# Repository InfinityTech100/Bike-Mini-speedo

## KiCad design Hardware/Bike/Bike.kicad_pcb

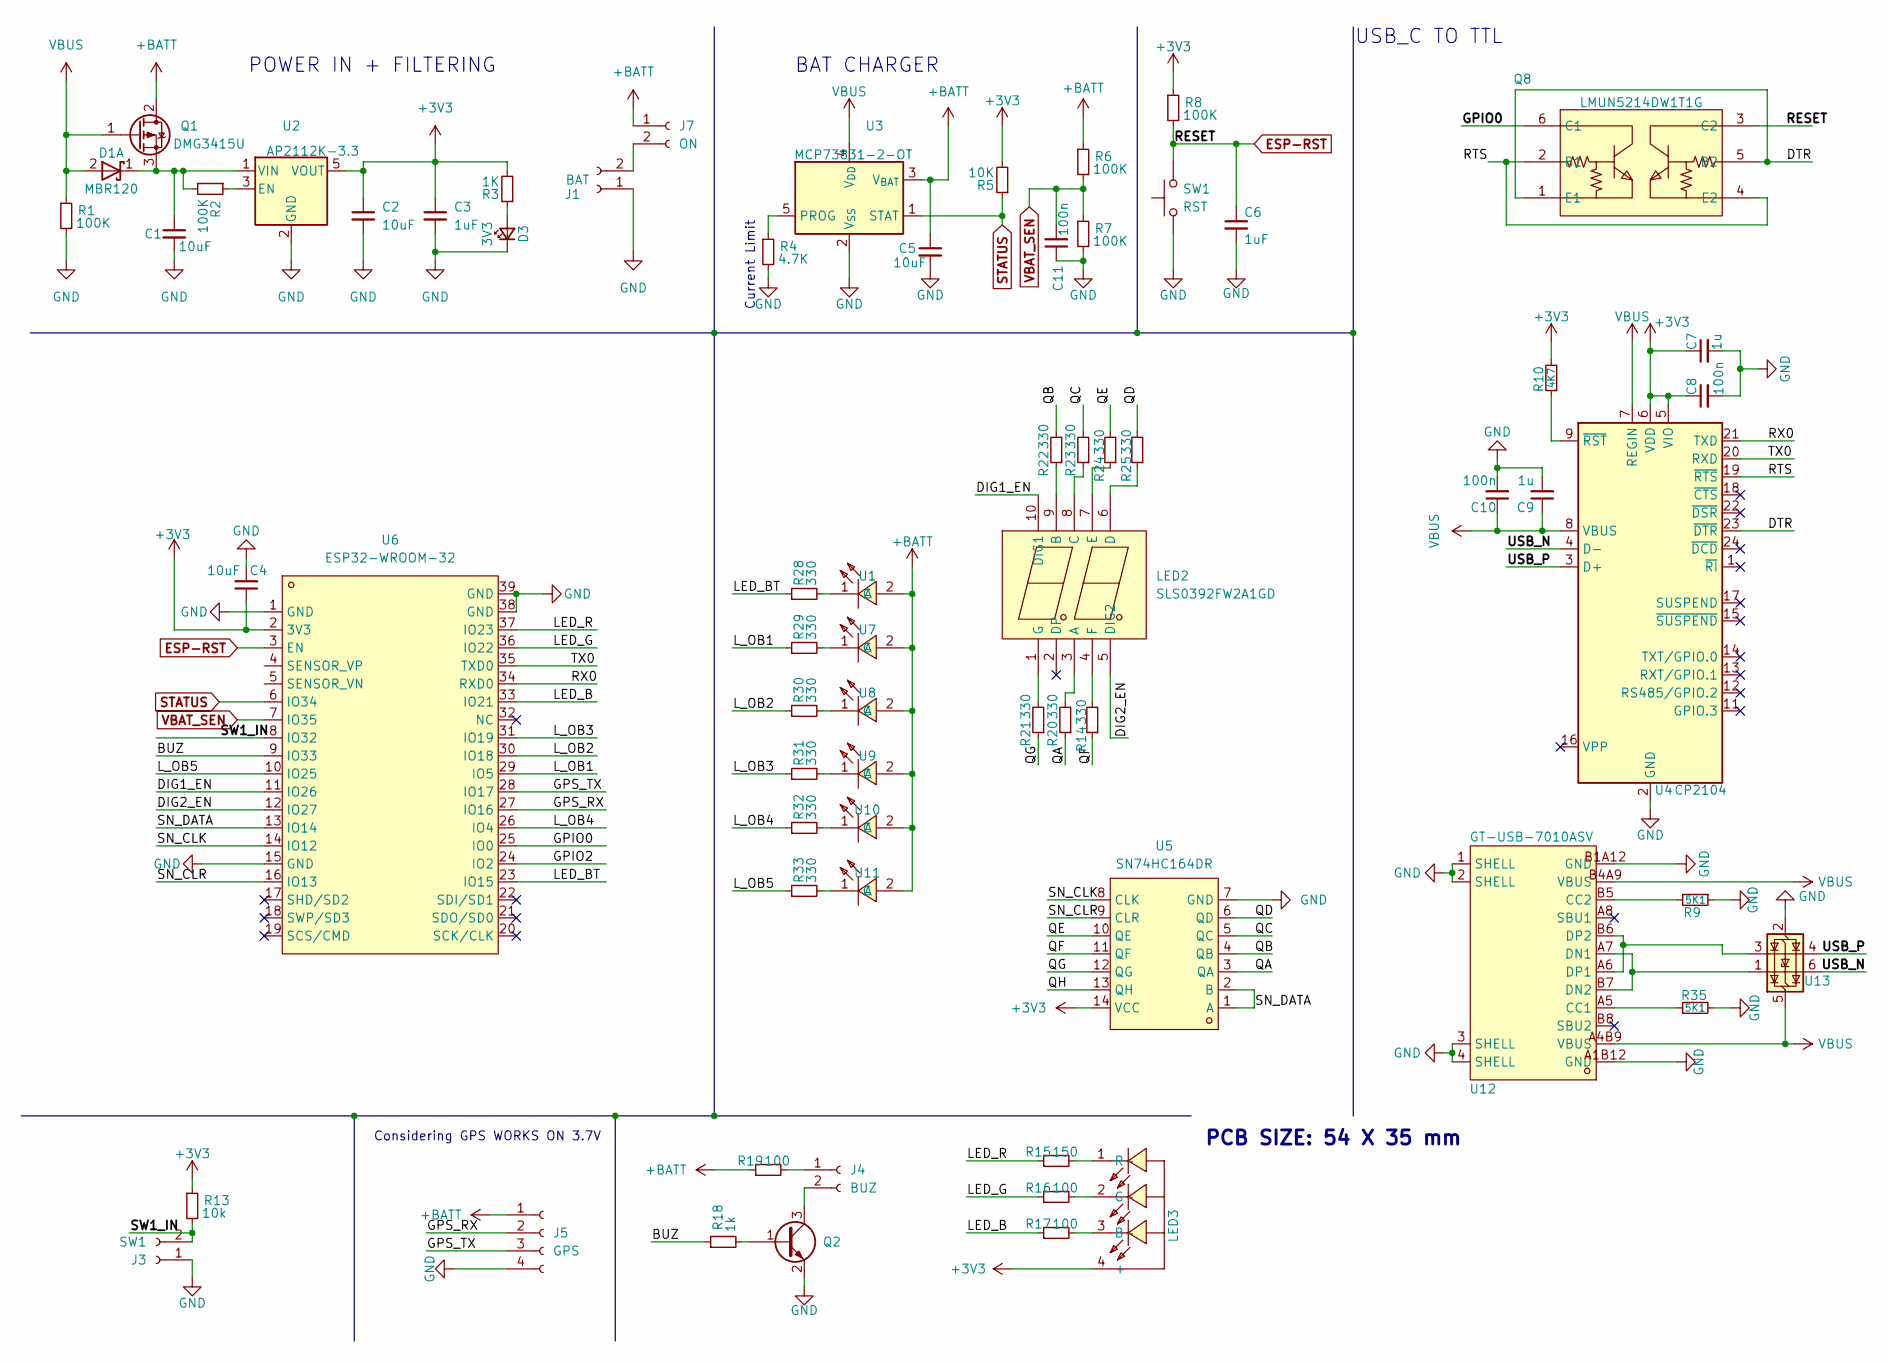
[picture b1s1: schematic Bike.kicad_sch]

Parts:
C1, C2, C4, C5: 10uF; C_0402_1005Metric
C3, C6: 1uF; C_0402_1005Metric
C7, C9: 1u; C_0402_1005Metric
C8, C10, C11: 100n; C_0402_1005Metric
D1: MBR120; D_SOD-123; LCSC C7422640
D3: 3V3; LED_0402_1005Metric
J1: BAT; PinSocket_1x02_P2.54mm_Vertical
J3: SW1; PinSocket_1x02_P2.54mm_Vertical
J4: BUZ; PinSocket_1x02_P2.54mm_Vertical_SMD_Pin1Left
J5: GPS; PinSocket_1x04_P2.54mm_Vertical
J7: ON; PinSocket_1x02_P2.54mm_Vertical
LED2: SLS0392FW2A1GD; LED-SEG-SMD_SLS0392FW2A1GD; LCSC Part C226001
LED3: 19-037A/RSGHBHW1-S03/2T; LED-ARRAY-SMD_4P-L1.6-W1.6-TR_EVERLIGHT_RSGHBHW1-S03; LCSC Part C282128
Q1: DMG3415U; SOT-23; LCSC C96616
Q2: Q_NPN_BEC; SOT-23-3
Q8: LMUN5214DW1T1G; SOT-363_L2.0-W1.3-P0.65-LS2.1-TL; LCSC Part C136173
R1, R2, R6, R7, R8: 100K; R_0402_1005Metric_Pad0.72x0.64mm_HandSolder
R3: 1K; R_0402_1005Metric_Pad0.72x0.64mm_HandSolder
R4: 4.7K; R_0402_1005Metric_Pad0.72x0.64mm_HandSolder
R5: 10K; R_0402_1005Metric_Pad0.72x0.64mm_HandSolder
R9, R35: 5K1; R_0402_1005Metric_Pad0.72x0.64mm_HandSolder
R10: 4K7; R_0402_1005Metric_Pad0.72x0.64mm_HandSolder
R13: 10k; R_0402_1005Metric_Pad0.72x0.64mm_HandSolder
R14, R20, R21, R22, R23, R24, R25, R28, R29, R30, R31, R32, R33: 330; R_0402_1005Metric_Pad0.72x0.64mm_HandSolder
R15: 150; R_0402_1005Metric; LCSC C445579
R16, R17, R19: 100; R_0402_1005Metric; LCSC C186115
R18: 1k; R_0402_1005Metric_Pad0.72x0.64mm_HandSolder
SW1: RST; PinSocket_1x02_P2.54mm_Vertical
U1: APTD3216SECK; LED1206-RD; LCSC Part C5569593
U2: AP2112K-3.3; SOT-23-5; LCSC C3021085
U3: MCP73831-2-OT; SOT-23-5
U4: CP2104; QFN-24-1EP_4x4mm_P0.5mm_EP2.6x2.6mm; LCSC C47742
U5: SN74HC164DR; SOIC-14_L8.7-W3.9-P1.27-LS6.0-BL; LCSC Part C5419
U6: ESP32-WROOM-32; WIFIM-SMD_ESP32-WROOM-32-N4; LCSC Part C82899
U7, U8, U9, U10, U11: APTD3216SECK; LED1206-RD; LCSC Part C5879029
U12: GT-USB-7010ASV; USB-C-SMD_G-SWITCH_GT-USB-7010ASV; LCSC Part C2988369
U13: USBLC6-2P6; SOT-666; LCSC C2827693

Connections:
+3V3: C2.1, C3.1, C4.1, C7.1, C8.1, LED3.4 (+), R3.2, R5.2, R8.1, R10.2, R13.1, U2.5 (VOUT), U4.5 (VIO), U4.6 (VDD), U5.14 (VCC), U6.2 (3V3)
+BATT: C5.1, J5.1, J7.1, Q1.2 (D), R6.1, R19.1, U1.2 (A), U3.3 (V_{BAT}), U7.2 (A), U8.2 (A), U9.2 (A), U10.2 (A), U11.2 (A)
/BUZ: R18.1, U6.9 (IO33)
/DIG1_EN: LED2.10 (DIG1), U6.11 (IO26)
/DIG2_EN: LED2.5 (DIG2), U6.12 (IO27)
/DTR: Q8.1 (E1), Q8.5 (B2), U4.23 (~DTR)
/GPIO0: Q8.6 (C1), U6.25 (IO0)
/GPIO2: U6.24 (IO2)
/GPS_RX: J5.2, U6.27 (IO16)
/GPS_TX: J5.3, U6.28 (IO17)
/LED_B: R17.1, U6.33 (IO21)
/LED_BT: R28.1, U6.23 (IO15)
/LED_G: R16.1, U6.36 (IO22)
/LED_R: R15.1, U6.37 (IO23)
/L_OB1: R29.1, U6.29 (IO5)
/L_OB2: R30.1, U6.30 (IO18)
/L_OB3: R31.1, U6.31 (IO19)
/L_OB4: R32.1, U6.26 (IO4)
/L_OB5: R33.1, U6.10 (IO25)
/QA: R20.1, U5.3 (QA)
/QB: R22.2, U5.4 (QB)
/QC: R23.2, U5.5 (QC)
/QD: R25.2, U5.6 (QD)
/QE: R24.2, U5.10 (QE)
/QF: R14.1, U5.11 (QF)
/QG: R21.1, U5.12 (QG)
/QH: U5.13 (QH)
/RTS: Q8.2 (B1), Q8.4 (E2), U4.19 (~RTS)
/RX0: U4.21 (TXD), U6.34 (RXD0)
/SN_CLK: U5.8 (CLK), U6.14 (IO12)
/SN_CLR: U5.9 (CLR), U6.16 (IO13)
/SN_DATA: U5.1 (A), U5.2 (B), U6.13 (IO14)
/SW1_IN: J3.2, R13.2, U6.8 (IO32)
/TX0: U4.20 (RXD), U6.35 (TXD0)
/USB_N: U4.4 (D-), U13.6 (I/O1)
/USB_P: U4.3 (D+), U13.4 (I/O2)
ESP-RST: C6.1, Q8.3 (C2), R8.2, SW1.2, U6.3 (EN)
GND: C1.2, C2.2, C3.2, C4.2, C5.2, C6.2, C7.2, C8.2, C9.2, C10.2, C11.1, D3.1 (K), J1.1, J3.1, J5.4, Q2.2 (E), R1.2, R4.2, R7.2, R9.1, R35.2, SW1.1, U2.2 (GND), U3.2 (V_{SS}), U4.2 (GND), U4.25 (GND), U5.7 (GND), U6.1 (GND), U6.15 (GND), U6.38 (GND), U6.39 (GND), U12.1 (SHELL), U12.2 (SHELL), U12.3 (SHELL), U12.4 (SHELL), U12.A1B12 (GND), U12.B1A12 (GND), U13.2 (GND)
unnamed: C1.1, D1.1 (K), Q1.3 (S), R2.2, U2.1 (VIN)
unnamed: D3.2 (A), R3.1
unnamed: J1.2, J7.2
unnamed: J4.1, R19.2
unnamed: J4.2, Q2.3 (C)
unnamed: LED2.3 (A), R20.2
unnamed: LED2.9 (B), R22.1
unnamed: LED2.8 (C), R23.1
unnamed: LED2.6 (D), R25.1
unnamed: LED2.7 (E), R24.1
unnamed: LED2.4 (F), R14.2
unnamed: LED2.1 (G), R21.2
unnamed: LED3.3 (B-), R17.2
unnamed: LED3.2 (G-), R16.2
unnamed: LED3.1 (R-), R15.2
unnamed: Q2.1 (B), R18.2
unnamed: R28.2, U1.1 (C)
unnamed: R2.1, U2.3 (EN)
unnamed: R4.1, U3.5 (PROG)
unnamed: R10.1, U4.9 (~RST)
unnamed: R29.2, U7.1 (C)
unnamed: R30.2, U8.1 (C)
unnamed: R31.2, U9.1 (C)
unnamed: R32.2, U10.1 (C)
unnamed: R33.2, U11.1 (C)
unnamed: R35.1, U12.A5 (CC1)
unnamed: R9.2, U12.B5 (CC2)
unnamed: U12.A7 (DN1), U12.B7 (DN2), U13.1 (I/O1)
unnamed: U12.A6 (DP1), U12.B6 (DP2), U13.3 (I/O2)
STATUS: R5.1, U3.1 (STAT), U6.6 (IO34)
VBAT_SEN: C11.2, R6.2, R7.1, U6.7 (IO35)
VBUS: C9.1, C10.1, D1.2 (A), Q1.1 (G), R1.1, U3.4 (V_{DD}), U4.7 (REGIN), U4.8 (VBUS), U12.A4B9 (VBUS), U12.B4A9 (VBUS), U13.5 (VBUS)

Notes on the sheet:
PCB SIZE: 54 X 35 mm
Current Limit
USB_C TO TTL
Considering GPS WORKS ON 3.7V
BAT CHARGER
POWER IN + FILTERING

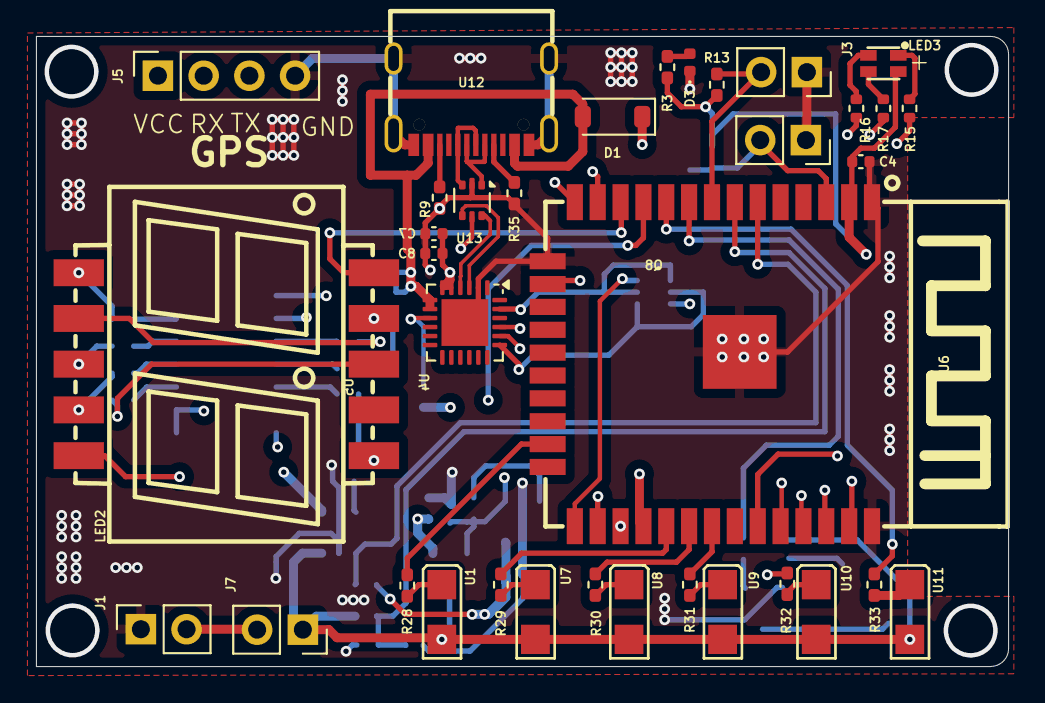
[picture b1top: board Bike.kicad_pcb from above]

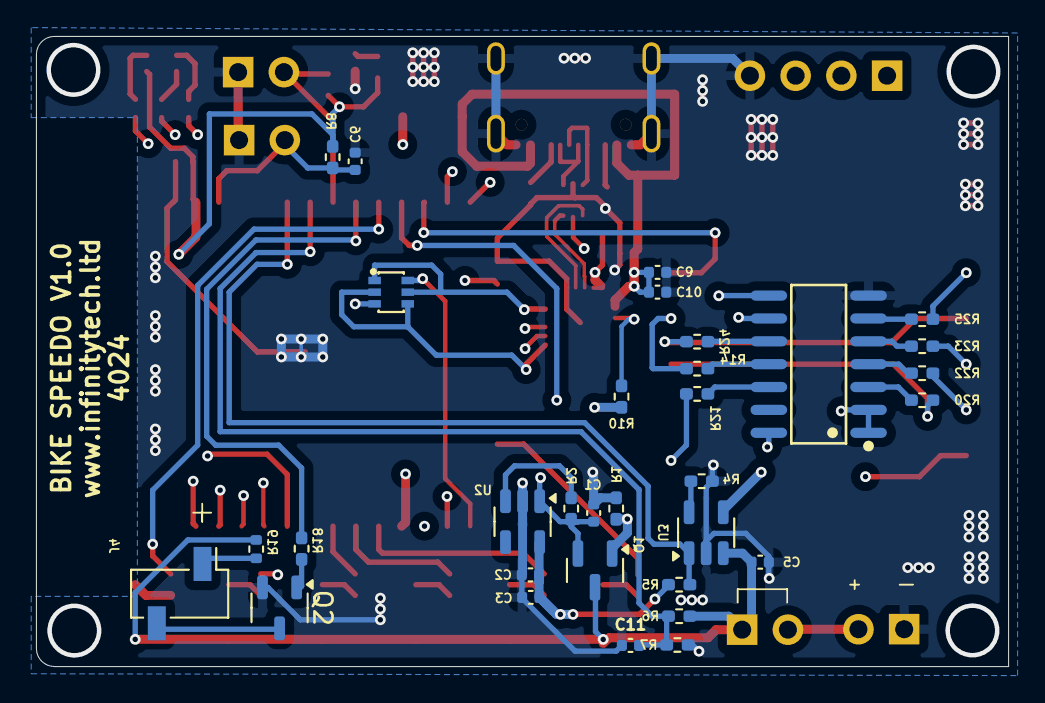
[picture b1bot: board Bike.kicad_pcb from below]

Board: 4 copper layers, 54.0 x 35.0 mm, 67 parts (32 on the bottom side), 68 nets.

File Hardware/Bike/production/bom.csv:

Designator,Footprint,Quantity,Value,LCSC Part #
"C1, C2, C4, C5",0402,4,10uF,
"C10, C11, C8",0402,3,100n,
"C3, C6",0402,2,1uF,
"C7, C9",0402,2,1u,
D1,D_SOD-123,1,MBR120,C7422640
D3,0402,1,3V3,
J1,PinSocket_1x02_P2.54mm_Vertical,1,BAT,
J3,PinSocket_1x02_P2.54mm_Vertical,1,SW1,
J4,PinSocket_1x02_P2.54mm_Vertical_SMD_Pin1Left,1,BUZ,
J5,PinSocket_1x04_P2.54mm_Vertical,1,GPS,
J7,PinSocket_1x02_P2.54mm_Vertical,1,ON,
LED2,LED-SEG-SMD_SLS0392FW2A1GD,1,SLS0392FW2A1GD,C226001
LED3,LED-ARRAY-SMD_4P-L1.6-W1.6-TR_EVERLIGHT_RSGHBHW1-S03,1,19-037A/RSGHBHW1-S03/2T,C282128
Q1,SOT-23,1,DMG3415U,
Q2,SOT-23-3,1,Q_NPN_BEC,
Q8,SOT-363_L2.0-W1.3-P0.65-LS2.1-TL,1,LMUN5214DW1T1G,C136173
"R1, R2, R6, R7, R8",0402,5,100K,
R10,0402,1,4K7,
"R13, R5",0402,2,10k,
"R14, R20, R21, R22, R23, R24, R25, R28, R29, R30, R31, R32, R33",0402,13,330,
R15,0402,1,150,C445579
"R16, R17, R19",0402,3,100,C186115
"R18, R3",0402,2,1k,
"R35, R9",0402,2,5K1,
R4,0402,1,4.7K,
SW1,PinSocket_1x02_P2.54mm_Vertical,1,RST,
U1,LED1206-RD,1,APTD3216SECK,C5569593
"U10, U11, U7, U8, U9",LED1206-RD,5,APTD3216SECK,C5879029
U12,USB-C-SMD_G-SWITCH_GT-USB-7010ASV,1,GT-USB-7010ASV,C2988369
U13,SOT-666,1,USBLC6-2P6,C2827693
U2,SOT-23-5,1,AP2112K-3.3,C3021085
U3,SOT-23-5,1,MCP73831-2-OT,
U4,QFN-24-1EP_4x4mm_P0.5mm_EP2.6x2.6mm,1,CP2104,C47742
U5,SOIC-14_L8.7-W3.9-P1.27-LS6.0-BL,1,SN74HC164DR,C5419
U6,WIFIM-SMD_ESP32-WROOM-32-N4,1,ESP32-WROOM-32,C82899

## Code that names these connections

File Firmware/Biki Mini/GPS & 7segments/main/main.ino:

#include <SoftwareSerial.h>
#include <TinyGPS++.h>

/* Define TX and RX pins for SoftwareSerial */ 
#define   GPS_RX_PIN   16   /* Pin for GPS RX signal IO16 */
#define   GPS_TX_PIN   17   /* Pin for GPS TX signal IO17 */

/* Define pin assignments for the 7-segment display and common Cathodes */ 
#define   CLOCKPIN    12   /* Pin for clock signal IO12 */ 
#define   LATCHPIN    13   /* Pin for latch signal IO13 */  
#define   DATAPIN     14   /* Pin for data  signal IO14 */ 

#define   COMMON1PIN  26   /* Pin for common cathode DIG1_EN IO26 */ 
#define   COMMON2PIN  27   /* Pin for common cathode DIG2_EN IO27 */

/* Create a TinyGPS++ object */ 
TinyGPSPlus gps;

/* Define SoftwareSerial object for GPS communication */
SoftwareSerial gpsSerial(GPS_RX_PIN, GPS_TX_PIN);
 
/* Function prototype to display a number on the 7-segment display */
void displayNumber(int number);

/* Binary representation of each digit from 0 to 9 for the 7-segment display */
const byte segments[] = 
{
  B00111111, /* 0 */
  B00000110, /* 1 */
  B01011011, /* 2 */
  B01001111, /* 3 */
  B01100110, /* 4 */
  B01101101, /* 5 */
  B01111101, /* 6 */
  B00000111, /* 7 */
  B01111111, /* 8 */
  B01101111  /* 9 */
};
void setup()
{
  Serial.begin(9600);    /* Initialize serial monitor */
  gpsSerial.begin(9600); /* Initialize GPS serial communication */
  /* Set pin modes for all pins used */ 
  pinMode(LATCHPIN, OUTPUT);
  pinMode(CLOCKPIN, OUTPUT);
  pinMode(DATAPIN, OUTPUT);
  pinMode(COMMON1PIN, OUTPUT);
  pinMode(COMMON2PIN, OUTPUT);

}

void loop()
{
  while (gpsSerial.available() > 0) 
  {
    gps.encode(gpsSerial.read()); /* Feed GPS data to TinyGPS++ */
  }
  /* Check if new GPS data is available */ 
  if (gps.location.isUpdated()) 
  {
    /* Get latitude and longitude */ 
    Serial.print("Latitude: ");
    Serial.println(gps.location.lat(), 8);
    Serial.print("Longitude: ");
    Serial.println(gps.location.lng(), 8);
  }
  /* Check if speed data is available */
  if (gps.speed.isUpdated()) 
  { 
    /* Convert speed to kilometers per hour */
    float speed = gps.speed.kmph();
    Serial.print("Speed (km/h): ");
    Serial.println(speed);
    displayNumber(speed);
  }
  /* Wait a bit before reading GPS data again */
  delay(1000);
}
void displayNumber(float number)
{

  int tens  = (int)number / 10;/* Extract tens digit  */
  int units = (int)number % 10;/* Extract units digit */

  /* Display tens digit on DIG1 */
  digitalWrite(COMMON1PIN, HIGH);
  digitalWrite(COMMON2PIN, LOW);
  digitalWrite(LATCHPIN, LOW);
  shiftOut(DATAPIN, CLOCKPIN, MSBFIRST, segments[tens]);
  digitalWrite(LATCHPIN, HIGH);
  delay(10);

  /* Display units digit on DIG2 */
  digitalWrite(COMMON1PIN, LOW);
  digitalWrite(COMMON2PIN, HIGH);
  digitalWrite(LATCHPIN, LOW);
  shiftOut(DATAPIN, CLOCKPIN, MSBFIRST, segments[units]);
  digitalWrite(LATCHPIN, HIGH);
  delay(10); 
}

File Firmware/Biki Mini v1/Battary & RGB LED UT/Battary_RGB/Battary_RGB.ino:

#include <Arduino.h>
#include <BLEDevice.h>
#include <SoftwareSerial.h>
#include <TinyGPS++.h>

#define   LED_R         22
#define   LED_G         21
#define   LED_B         23
#define   BATT_VOLTAGE  35
#define   CHG_STATUS    34
uint32_t Tick_counter2 = 0;
uint8_t prev_batt_percentage = 0;
int batt_val = 0;
uint8_t batt_percentage = 0;
bool firstTime =false;

void setup() 
{
  Serial.begin(115200);
  pinMode(BATT_VOLTAGE, INPUT_PULLDOWN);
  pinMode(LED_R, OUTPUT);
  pinMode(LED_G, OUTPUT);
  pinMode(LED_B, OUTPUT);
  digitalWrite(LED_R, LOW);
  digitalWrite(LED_G, LOW);
  digitalWrite(LED_B, LOW);
  pinMode(CHG_STATUS, INPUT);
}

void loop() 
{
  if ((millis() - Tick_counter2) >= 500) {
    // measure battery voltage and change RGB status according to battery level
    batt_lvl_check();
    Tick_counter2 = millis();
  }
}
void batt_lvl_check(void) {
  //get the current
  batt_val = analogRead(BATT_VOLTAGE);
  batt_percentage = map(batt_val, 2620, 4095, 0, 100);
  uint8_t chg_stat = digitalRead(CHG_STATUS);

  if (batt_percentage >= 0 && batt_percentage <= 30) 
  {
    if (chg_stat == HIGH) 
    {
      //toggle led for blinking if it's in charging mode
      digitalWrite(LED_R, !digitalRead(LED_R));
    } 
    else 
    {
      digitalWrite(LED_R, HIGH);
    }
    digitalWrite(LED_G, LOW);
    digitalWrite(LED_B, LOW);

  } 
  else if (batt_percentage > 30 && batt_percentage <= 70) 
  {
    if (chg_stat == HIGH) {
      //toggle led for blinking if it's in charging mode
      digitalWrite(LED_G, !digitalRead(LED_G));
    } 
    else 
    {
      digitalWrite(LED_G, HIGH);
    }
    digitalWrite(LED_R, LOW);
    digitalWrite(LED_B, LOW);
  } 
  else if (batt_percentage > 70 && batt_percentage <= 100) 
  {
    if (chg_stat == HIGH) {
      //toggle led for blinking if it's in charging mode
      digitalWrite(LED_B, !digitalRead(LED_B));
    } else {
      digitalWrite(LED_B, HIGH);
    }
    digitalWrite(LED_R, LOW);
    digitalWrite(LED_G, LOW);
  }
  if ((firstTime) && (batt_percentage > 100 || (abs(prev_batt_percentage - batt_percentage) >= 10))) 
  {
    Serial.println("ERROR READING BATT VOLRAGE!!");
    batt_percentage = prev_batt_percentage;
  } 
  else 
  {
    prev_batt_percentage = batt_percentage;
  }
  Serial.print("Battery Percentage =");
  Serial.println(batt_percentage);
  firstTime = true;
}

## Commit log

2024-03-07 Bike Documents & Datasheets
2024-03-07 Hardware Schematic
2024-03-07 Updated Schematic
2024-03-07 adde schematic as pdf
2024-03-12 schematics design
2024-03-16 Added the 74H595 shift register to HW schematic and tested the 2digit 7segmments using the shitf register
2024-03-18 GPS & 7Segments test code
2024-03-21 The first version of Bike mini speedo code v0
2024-03-25 Moblie_App v0
2024-03-25 made leds states changeable
2024-03-25 changed the UI for urad3 V1
2024-03-26 Speed feature add & BLE communication
2024-03-29 Bike Mini v1
2024-03-29 fixed padding problem
2024-03-29 fixed bike indecator problem + speed
2024-04-02 Urad3 V2 Fixed battery & drawer menu Bug
2024-04-02 Urad3 homPage modify
2024-04-22 modified the Flash Characteristic
2024-04-29 hardware done
2024-05-02 Finished unite Testing all pcb components & added the Bike v1 code
2024-05-10 The last version of Bike Speedo
2024-05-11 fixing testing note
2024-05-26 Added the Battery Level feature to the app + updated firmware to match the chabges in the frame
2024-06-13 Modified Battery widget
2024-06-13 pcb fix again
